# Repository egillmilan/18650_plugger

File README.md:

# 18650 plugger
A carrier board for a single 18650 Li-ion cell with all the appropriate protection and charging circuitry. The idea is to have a simple plug-and-play solution for batterizing any electronics project without having to deal with all the hassle of Li-ion batteries. The board also includes an OR-contoller allowing for the project to run on the power from the charger while the battery is getting charged. Note that this requires a charger that is able to provide enough current to charge the battery and power the project simultaneously.

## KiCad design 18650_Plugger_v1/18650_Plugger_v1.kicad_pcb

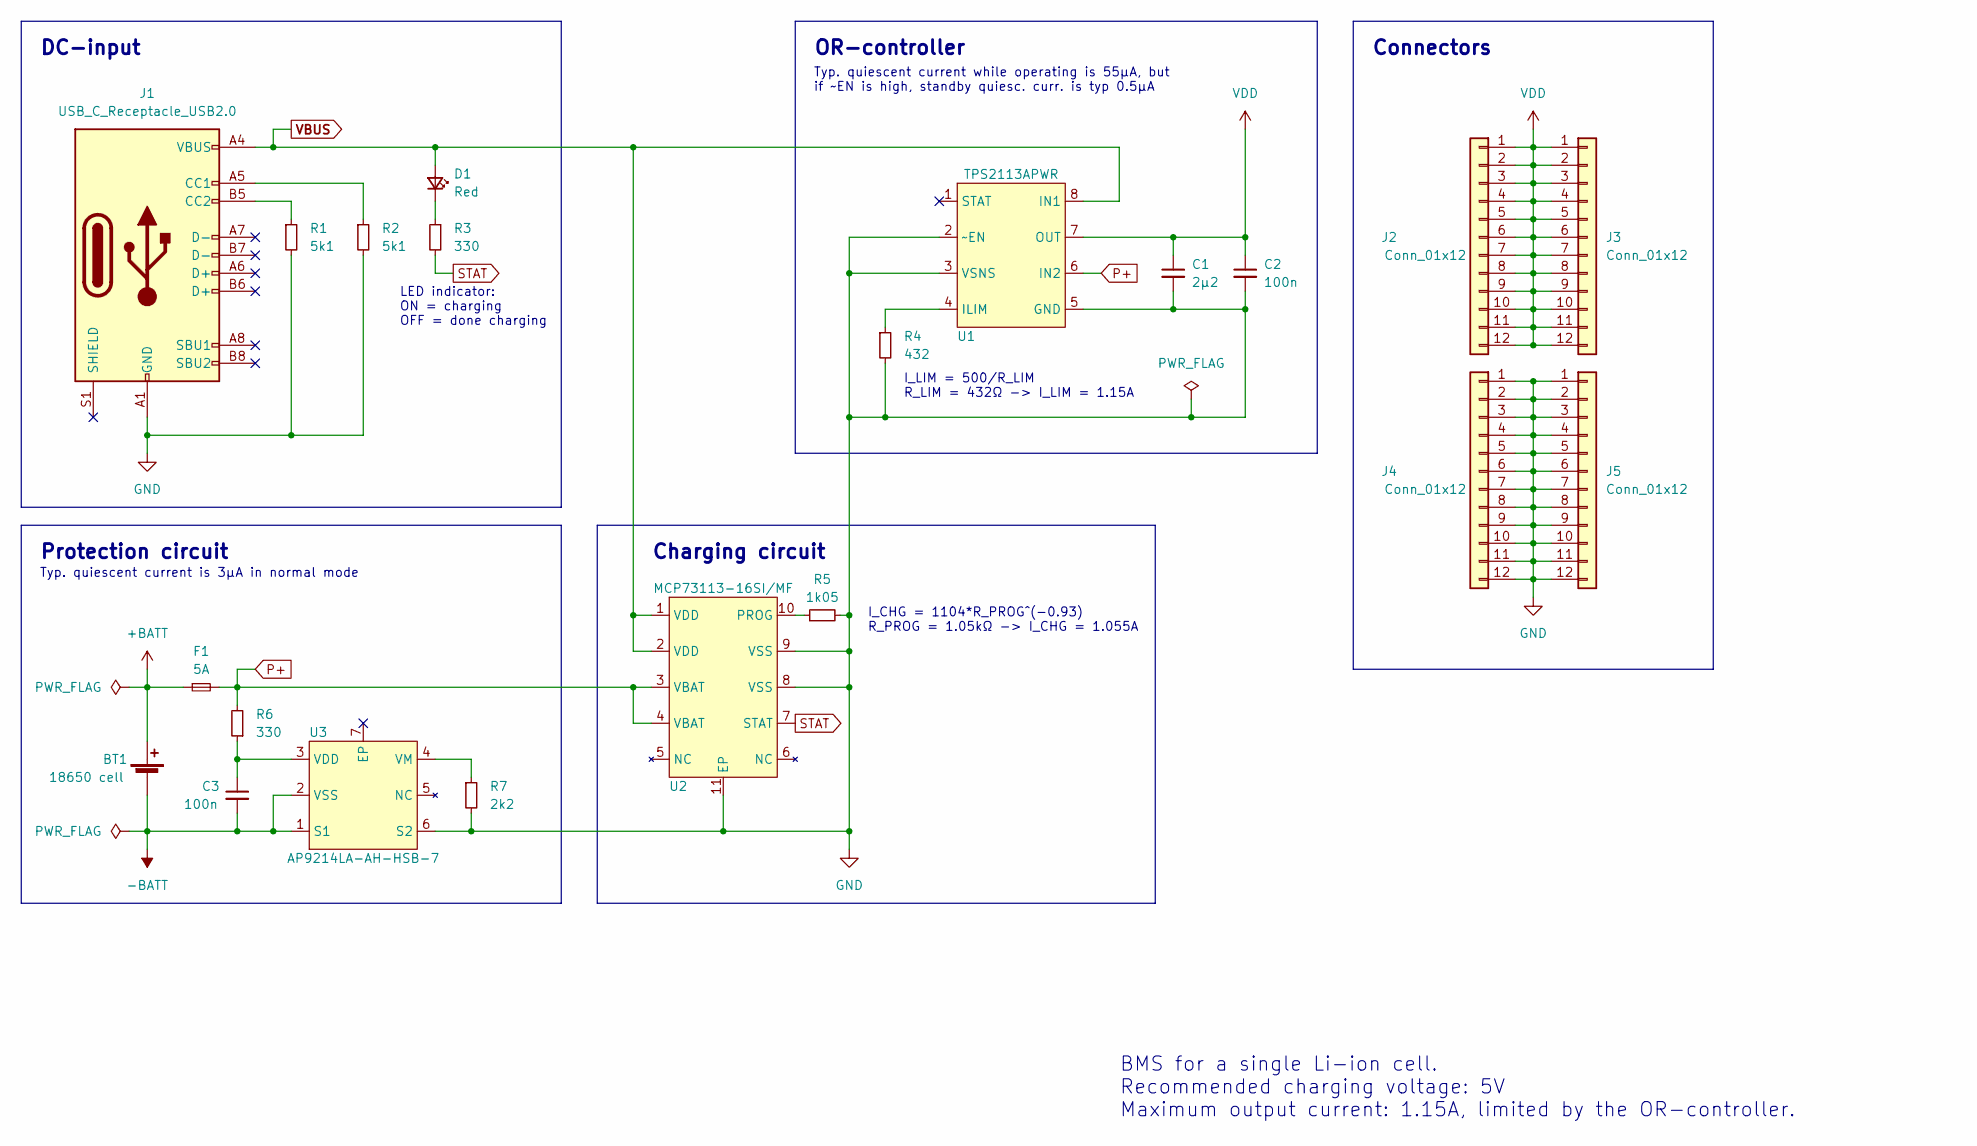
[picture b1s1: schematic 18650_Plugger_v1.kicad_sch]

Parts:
BT1: 18650 cell; Keystone_254_holder
C1: 2µ2; C_0805_2012Metric
C2, C3: 100n; C_0805_2012Metric
D1: Red; LED_0805_2012Metric
F1: 5A; Fuse_0805_2012Metric
J1: USB_C_Receptacle_USB2.0; GCT_USB4085-GF-A
J2, J3, J4, J5: Conn_01x12; PinHeader_1x12_P2.54mm_Vertical
R1, R2: 5k1; R_0805_2012Metric
R3, R6: 330; R_0805_2012Metric
R4: 432; R_0805_2012Metric
R5: 1k05; R_0805_2012Metric
R7: 2k2; R_0805_2012Metric
U1: TPS2113APWR; TSSOP-8_4.4x3mm_P0.65mm
U2: MCP73113-16SI/MF; DFN-10-1EP_3x3mm_P0.5mm_EP1.55x2.48mm
U3: AP9214LA-AH-HSB-7; U-DFN2535-6 (Type B)

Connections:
+BATT: BT1.1 (+), F1.1
-BATT: BT1.2 (-), C3.2, U3.1 (S1), U3.2 (VSS)
GND: C1.2, C2.2, J1.A1 (GND), J1.A12 (GND), J1.B1 (GND), J1.B12 (GND), J4.1, J4.2, J4.3, J4.4, J4.5, J4.6, J4.7, J4.8, J4.9, J4.10, J4.11, J4.12, J5.1, J5.2, J5.3, J5.4, J5.5, J5.6, J5.7, J5.8, J5.9, J5.10, J5.11, J5.12, R1.2, R2.2, R4.2, R5.2, R7.2, U1.2 (~EN), U1.3 (VSNS), U1.5 (GND), U2.8 (VSS), U2.9 (VSS), U2.11 (EP), U3.6 (S2)
unnamed: C3.1, R6.1, U3.3 (VDD)
unnamed: D1.1 (K), R3.1
unnamed: J1.A5 (CC1), R2.1
unnamed: J1.B5 (CC2), R1.1
unnamed: R4.1, U1.4 (ILIM)
unnamed: R5.1, U2.10 (PROG)
unnamed: R7.1, U3.4 (VM)
P+: F1.2, R6.2, U1.6 (IN2), U2.3 (VBAT), U2.4 (VBAT)
STAT: R3.2, U2.7 (STAT)
VBUS: D1.2 (A), J1.A4 (VBUS), J1.A9 (VBUS), J1.B4 (VBUS), J1.B9 (VBUS), U1.8 (IN1), U2.1 (VDD), U2.2 (VDD)
VDD: C1.1, C2.1, J2.1, J2.2, J2.3, J2.4, J2.5, J2.6, J2.7, J2.8, J2.9, J2.10, J2.11, J2.12, J3.1, J3.2, J3.3, J3.4, J3.5, J3.6, J3.7, J3.8, J3.9, J3.10, J3.11, J3.12, U1.7 (OUT)

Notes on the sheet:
LED indicator: ON = charging OFF = done charging
Connectors
OR-controller
I_CHG = 1104*R_PROG^(-0.93) R_PROG = 1.05kΩ -> I_CHG = 1.055A
Typ. quiescent current is 3µA in normal mode
Charging circuit
BMS for a single Li-ion cell. Recommended charging voltage: 5V Maximum output current: 1.15A, limited by the OR-controller.
DC-input
Typ. quiescent current while operating is 55µA, but if ~EN is high, standby quiesc. curr. is typ 0.5µA
I_LIM = 500/R_LIM R_LIM = 432Ω -> I_LIM = 1.15A
Protection circuit

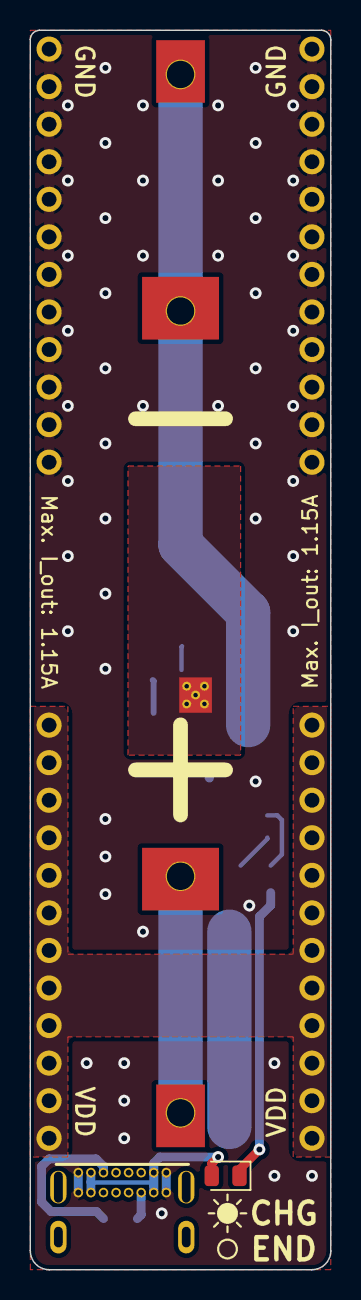
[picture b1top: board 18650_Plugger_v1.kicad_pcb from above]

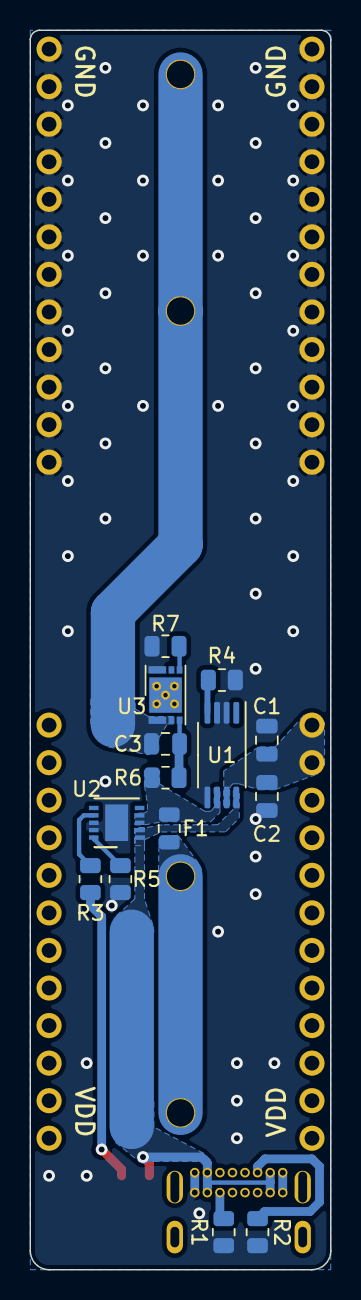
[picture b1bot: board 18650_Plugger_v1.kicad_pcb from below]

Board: 2 copper layers, 20.3 x 83.8 mm, 21 parts (18 on the bottom side), 14 nets.

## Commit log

2022-08-29 Schematic and PCB
2022-08-29 Clean up
2023-04-18 Images
